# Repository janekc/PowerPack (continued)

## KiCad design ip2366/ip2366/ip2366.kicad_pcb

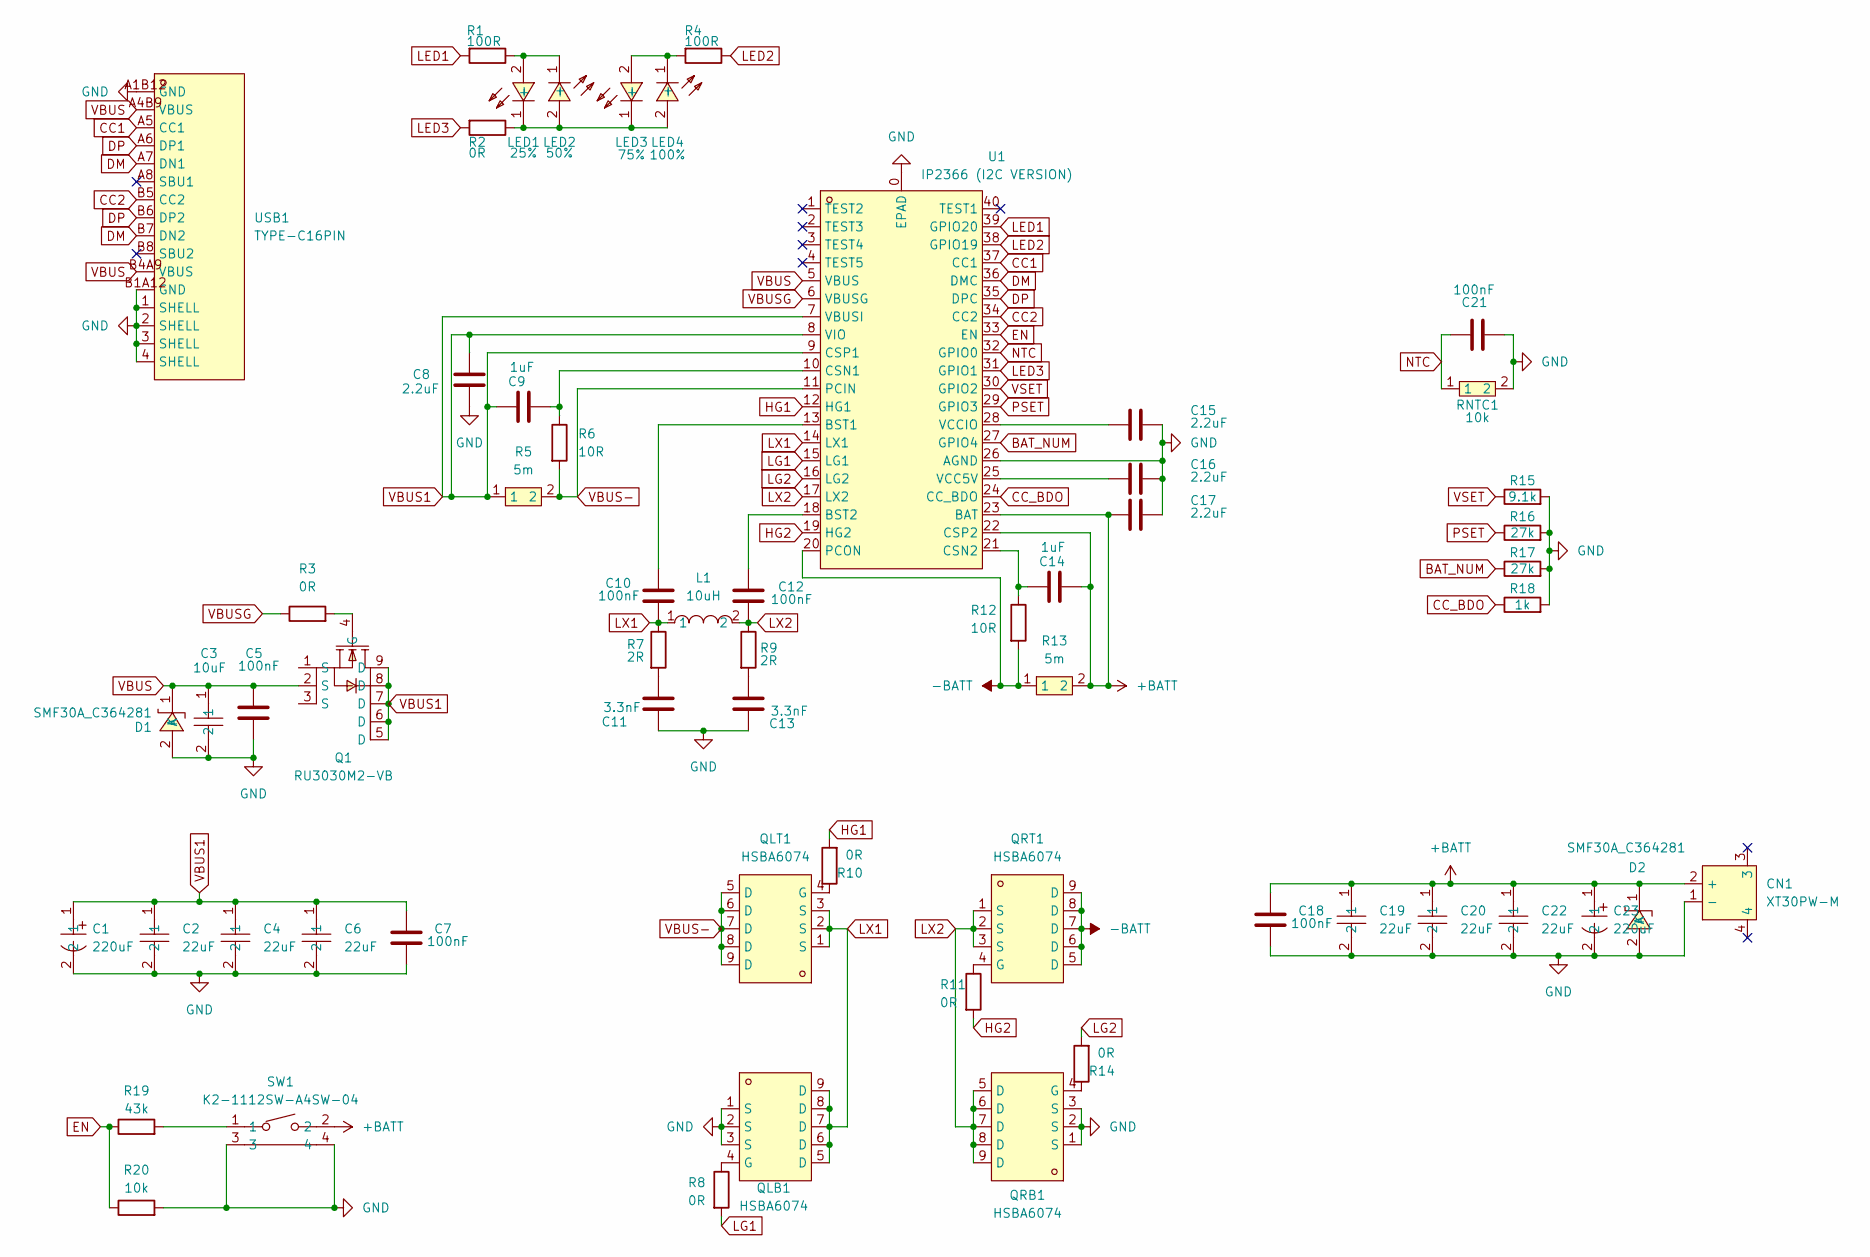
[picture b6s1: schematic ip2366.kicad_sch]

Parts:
C1, C23: 220uF; CAP-TH_BD8.0-P3.50-D0.6-FD; LCSC Part C2688260
C2, C4, C6, C19, C20, C22: 22uF; C1210; LCSC Part C778721
C3: 10uF; C1206; LCSC Part C89632
C5, C7, C10, C12, C18, C21: 100nF; C_0603_1608Metric_Pad1.08x0.95mm_HandSolder
C8, C15, C16, C17: 2.2uF; C_0603_1608Metric_Pad1.08x0.95mm_HandSolder
C9, C14: 1uF; C_0603_1608Metric_Pad1.08x0.95mm_HandSolder
C11, C13: 3.3nF; C_0603_1608Metric_Pad1.08x0.95mm_HandSolder
CN1: XT30PW-M; CONN-TH_XT30PW-M; LCSC Part C431092
D1, D2: SMF30A_C364281; SOD-123_L2.6-W1.6-LS3.5-RD; LCSC Part C364281
L1: 10uH; IND-SMD_L13.5-W12.5; LCSC Part C840531
LED1: 25%; LED0603-RD; LCSC Part C84265
LED2: 50%; LED0603-RD; LCSC Part C84265
LED3: 75%; LED0603-RD; LCSC Part C84265
LED4: 100%; LED0603-RD; LCSC Part C84265
Q1: RU3030M2-VB; DFN-8_L3.0-W3.0-P0.65-BL_VBQFXXXX; LCSC Part C19190164
QLB1: HSBA6074; DFN-8_L5.7-W5.1-P1.27-LS6.1-BL-2; LCSC Part C2903566
QLT1: HSBA6074; DFN-8_L5.7-W5.1-P1.27-LS6.1-BL-2; LCSC Part C2903566
QRB1: HSBA6074; DFN-8_L5.7-W5.1-P1.27-LS6.1-BL-2; LCSC Part C2903566
QRT1: HSBA6074; DFN-8_L5.7-W5.1-P1.27-LS6.1-BL-2; LCSC Part C2903566
R1, R4: 100R; R_0603_1608Metric_Pad0.98x0.95mm_HandSolder
R2, R3, R8, R10, R11, R14: 0R; R_0603_1608Metric_Pad0.98x0.95mm_HandSolder
R5, R13: 5m; R_2512_6332Metric_Pad1.40x3.35mm_HandSolder; LCSC Part C5123656
R6: 10R; R_0603_1608Metric_Pad0.98x0.95mm_HandSolder
R7, R9: 2R; R_0603_1608Metric_Pad0.98x0.95mm_HandSolder
R12: 10R; C_0603_1608Metric_Pad1.08x0.95mm_HandSolder
R15: 9.1k; R_0603_1608Metric_Pad0.98x0.95mm_HandSolder
R16, R17: 27k; R_0603_1608Metric_Pad0.98x0.95mm_HandSolder
R18: 1k; R_0603_1608Metric_Pad0.98x0.95mm_HandSolder
R19: 43k; R_0603_1608Metric_Pad0.98x0.95mm_HandSolder
R20: 10k; R_0603_1608Metric_Pad0.98x0.95mm_HandSolder
RNTC1: 10k; R0603; LCSC Part C98220
SW1: K2-1112SW-A4SW-04; KEY-TH_K2-1112SW-AXXW-XX; LCSC Part C223811
U1: IP2366 (I2C VERSION); QFN-40_L5.0-W5.0-P0.40-TL-EP3.7; LCSC Part C20415848
USB1: TYPE-C16PIN; USB-C-SMD_TYPE-C16PIN; LCSC Part C393939

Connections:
+BATT: C14.1, C17.2, C18.1, C19.1, C20.1, C22.1, C23.1, CN1.2 (+), D2.1 (K), R13.2, SW1.2, U1.22 (CSP2), U1.23 (BAT)
-BATT: QRT1.5 (D), QRT1.6 (D), QRT1.7 (D), QRT1.8 (D), QRT1.9 (D), R12.2, R13.1, U1.20 (PCON)
BAT_NUM: R17.1, U1.27 (GPIO4)
CC1: U1.37 (CC1), USB1.A5 (CC1)
CC2: U1.34 (CC2), USB1.B5 (CC2)
CC_BDO: R18.1, U1.24 (CC_BDO)
DM: U1.36 (DMC), USB1.A7 (DN1), USB1.B7 (DN2)
DP: U1.35 (DPC), USB1.A6 (DP1), USB1.B6 (DP2)
EN: R19.1, R20.1, U1.33 (EN)
GND: C1.2, C2.2, C3.2, C4.2, C5.2, C6.2, C7.2, C8.2, C11.2, C13.2, C15.1, C16.1, C17.1, C18.2, C19.2, C20.2, C21.2, C22.2, C23.2, CN1.1 (-), D1.2 (A), D2.2 (A), QLB1.1 (S), QLB1.2 (S), QLB1.3 (S), QRB1.1 (S), QRB1.2 (S), QRB1.3 (S), R15.2, R16.2, R17.2, R18.2, R20.2, RNTC1.2, SW1.3, SW1.4, U1.0 (EPAD), U1.26 (AGND), USB1.1 (SHELL), USB1.2 (SHELL), USB1.3 (SHELL), USB1.4 (SHELL), USB1.A1B12 (GND), USB1.B1A12 (GND)
HG1: R10.2, U1.12 (HG1)
HG2: R11.2, U1.19 (HG2)
LED1: R1.2, U1.39 (GPIO20)
LED2: R4.1, U1.38 (GPIO19)
LED3: R2.2, U1.31 (GPIO1)
LG1: R8.2, U1.15 (LG1)
LG2: R14.2, U1.16 (LG2)
LX1: C10.2, L1.1, QLB1.5 (D), QLB1.6 (D), QLB1.7 (D), QLB1.8 (D), QLB1.9 (D), QLT1.1 (S), QLT1.2 (S), QLT1.3 (S), R7.1, U1.14 (LX1)
LX2: C12.2, L1.2, QRB1.5 (D), QRB1.6 (D), QRB1.7 (D), QRB1.8 (D), QRB1.9 (D), QRT1.1 (S), QRT1.2 (S), QRT1.3 (S), R9.1, U1.17 (LX2)
unnamed: C11.1, R7.2
unnamed: C13.1, R9.2
unnamed: LED1.2 (+), LED2.1 (-), R1.1
unnamed: LED1.1 (-), LED2.2 (+), LED3.1 (-), LED4.2 (+), R2.1
unnamed: LED3.2 (+), LED4.1 (-), R4.2
unnamed: Q1.4 (G), R3.2
unnamed: QLB1.4 (G), R8.1
unnamed: QLT1.4 (G), R10.1
unnamed: QRB1.4 (G), R14.1
unnamed: QRT1.4 (G), R11.1
unnamed: R19.2, SW1.1
unnamed: C10.1, U1.13 (BST1)
unnamed: C12.1, U1.18 (BST2)
unnamed: C9.1, R6.1, U1.10 (CSN1)
unnamed: C14.2, R12.1, U1.21 (CSN2)
unnamed: C16.2, U1.25 (VCC5V)
unnamed: C15.2, U1.28 (VCCIO)
PSET: R16.1, U1.29 (GPIO3)
VBUS: C3.1, C5.1, D1.1 (K), Q1.1 (S), Q1.2 (S), Q1.3 (S), U1.5 (VBUS), USB1.A4B9 (VBUS), USB1.B4A9 (VBUS)
VBUS1: C1.1, C2.1, C4.1, C6.1, C7.1, C8.1, C9.2, Q1.5 (D), Q1.6 (D), Q1.7 (D), Q1.8 (D), Q1.9 (D), R5.1, U1.7 (VBUSI), U1.8 (VIO), U1.9 (CSP1)
VBUS-: QLT1.5 (D), QLT1.6 (D), QLT1.7 (D), QLT1.8 (D), QLT1.9 (D), R5.2, R6.2, U1.11 (PCIN)
VBUSG: R3.1, U1.6 (VBUSG)
VSET: R15.1, U1.30 (GPIO2)

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
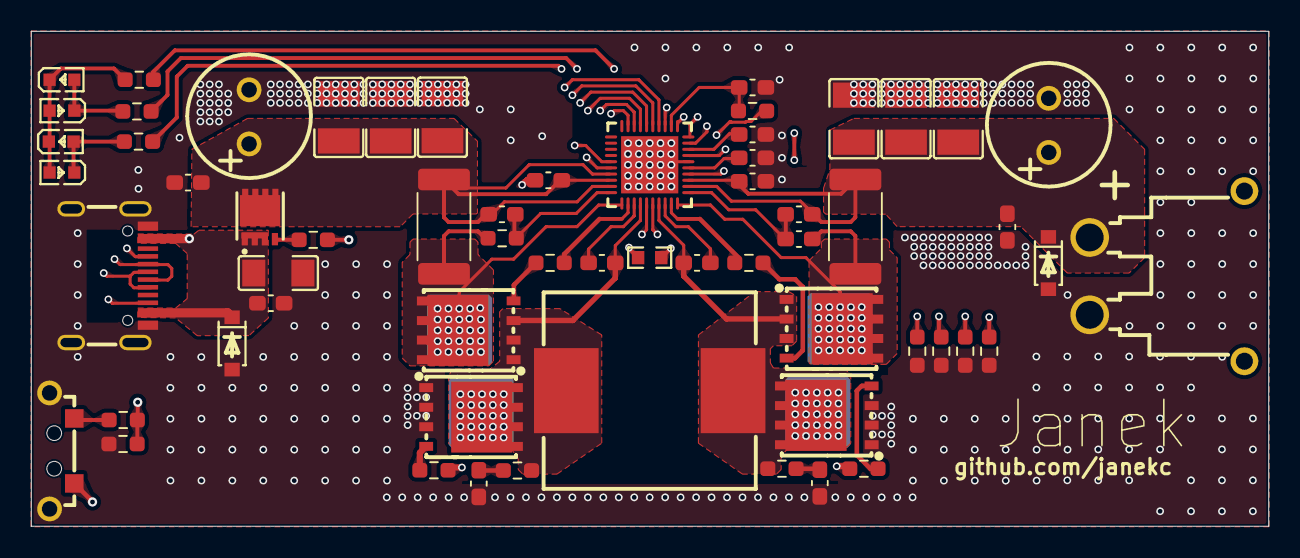
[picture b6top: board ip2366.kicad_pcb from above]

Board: 4 copper layers, 80.0 x 32.0 mm, 61 parts (0 on the bottom side), 44 nets.

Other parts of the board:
R21: 0R; R_0603_1608Metric_Pad0.98x0.95mm_HandSolder

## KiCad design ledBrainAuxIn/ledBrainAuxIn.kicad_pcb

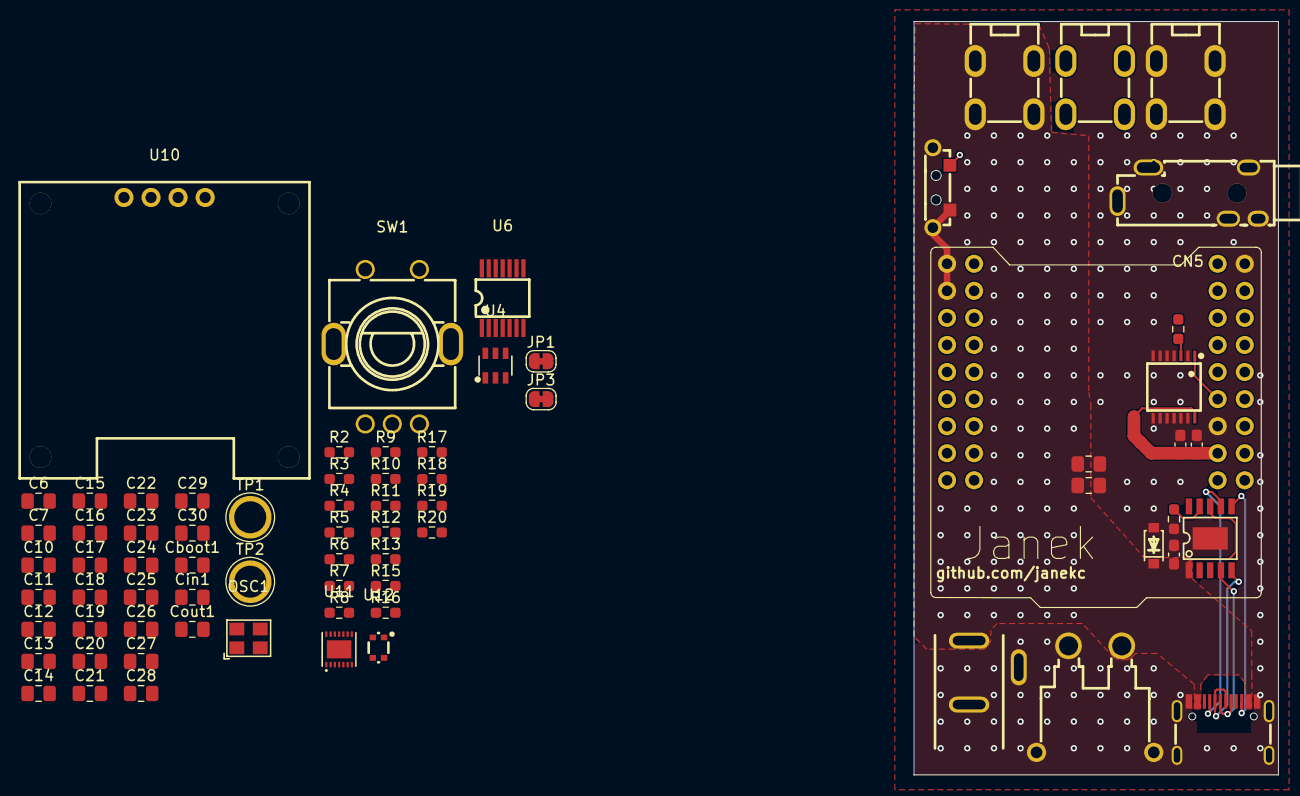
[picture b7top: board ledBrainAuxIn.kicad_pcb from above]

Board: 4 copper layers, 34.2 x 70.7 mm, 75 parts (1 on the bottom side), 49 nets.

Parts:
C1, C2: 0.1uF; C_0603_1608Metric_Pad1.08x0.95mm_HandSolder
C3: 1uF; C_0603_1608Metric_Pad1.08x0.95mm_HandSolder
C4, C5: 22uF; C_0805_2012Metric_Pad1.18x1.45mm_HandSolder
C6: 47pF; C_0805_2012Metric_Pad1.18x1.45mm_HandSolder
C7, C11, C15, C19: 100nF; C_0805_2012Metric_Pad1.18x1.45mm_HandSolder
C10, C12, C13, C14, C16, C17, C18: 10uF; C_0805_2012Metric_Pad1.18x1.45mm_HandSolder
C20: 15pF; C_0805_2012Metric_Pad1.18x1.45mm_HandSolder
C21, C22, C29, C30: 1uF; C_0805_2012Metric_Pad1.18x1.45mm_HandSolder
C23, C24, C25, C27, C28: 0.1uF; C_0805_2012Metric_Pad1.18x1.45mm_HandSolder
C26: 2.2uF; C_0805_2012Metric_Pad1.18x1.45mm_HandSolder
CN1: XT30PW-M; CONN-TH_XT30PW-M
CN5: PJ-328A0-B; AUDIO-TH_PJ-328A0-B
Cboot1: 1uF; C_0805_2012Metric_Pad1.18x1.45mm_HandSolder
Cin1: 10uF; C_0805_2012Metric_Pad1.18x1.45mm_HandSolder
Cout1: 10uF; C_0805_2012Metric_Pad1.18x1.45mm_HandSolder
D1: SMF30A_C364281; SOD-123_L2.6-W1.6-LS3.5-RD
DC1: DC-005-A200; DC-IN-TH_DC-005-A200
JP1, JP3: SolderJumper_2_Bridged; SolderJumper-2_P1.3mm_Bridged_RoundedPad1.0x1.5mm
OSC1: OT2EL4C4JI-111OLP-12.288M; OSC-SMD_4P-L3.2-W2.5-BL
R1: 62R; R_0603_1608Metric_Pad0.98x0.95mm_HandSolder
R2: 3.3M; R_0603_1608Metric_Pad0.98x0.95mm_HandSolder
R3: 5.1k; R_0603_1608Metric_Pad0.98x0.95mm_HandSolder
R4: 1k; R_0603_1608Metric_Pad0.98x0.95mm_HandSolder
R5, R6, R13, R16: 100R; R_0603_1608Metric_Pad0.98x0.95mm_HandSolder
R7, R8, R9, R10, R11, R12, R14, R15, R17, R18: 10k; R_0603_1608Metric_Pad0.98x0.95mm_HandSolder
R19: 150k or NC; R_0603_1608Metric_Pad0.98x0.95mm_HandSolder
R20: 100k or 0R; R_0603_1608Metric_Pad0.98x0.95mm_HandSolder
Rset1: 24k; R_0603_1608Metric_Pad0.98x0.95mm_HandSolder
SW1: EC11E09244BS; SW-TH_EC11XXXXXXXX
SW2: K2-1112SW-A4SW-04; KEY-TH_K2-1112SW-AXXW-XX
TP1: VDD; TestPoint_Plated_Hole_D3.0mm
TP2: GND; TestPoint_Plated_Hole_D3.0mm
U1: QuinLED-ESP32
U3: CH224A; ESSOP-10_L4.9-W3.9-P1.0-LS6.0-TL-EP
U4: ME3116; SOT-23-6_L2.9-W1.6-P0.95-LS2.8-BL
U5: SN74AHCT32QPWRQ1; TSSOP-14_L5.0-W4.4-P0.65-LS6.5-BL
U6: PCM1808PWR; TSSOP-14_L5.0-W4.4-P0.65-LS6.4-BL
U7, U8, U9: T34069; XFCN_PKT-TH_4P-T34069
U10: HS96L03W2C03; OLED-TH_L27.8-W27.2-P2.54_C9900033791
U11: MAX9814ETD+T; TDFN-14_L3.0-W3.0-P0.40-BL-EP
U12: NA-FFA381-A10-1; MIC-SMD_4P-L2.8-W1.9_NA-FFA381-A10-1
USB1: TYPE-C16PIN; USB-C-SMD_TYPE-C16PIN

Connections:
+3.3V: C17.1, C18.1, C19.1, C30.1, JP1.1 (A), OSC1.1 (Tri-state), OSC1.4 (VDD), R7.1, R8.1, R9.1, R15.1, R17.1, R18.1, U1.17 (3v3), U10.2 (VCC), U11.2 (~SHDN), U11.5 (VDD), U11.10 (GAIN)
+5V: C1.1, C2.2, C6.1, Cout1.2, JP3.1 (A), R3.1, R14.2, U1.26 (5v0), U5.14 (VCC)
AUDIO MCLK: C20.2, OSC1.3 (OUT), R5.2
AUDIO SCK: R16.1, U1.7 (IO14)
AUDIO SD: R13.1, U1.18 (IO13)
AUDIO WS: R6.2, U1.4 (IO35)
AUXIN_L: C16.1, CN5.2
AUXIN_R: C10.1, CN5.3
CC1: U3.7 (CC1), USB1.A5 (CC1)
CC2: U3.6 (CC2), USB1.B5 (CC2)
DISPLAY SCL: U1.31 (IO32), U10.3 (SCL)
DISPLAY SDA: U1.33 (IO_4), U10.4 (SDA)
DM: U3.5 (DM), USB1.A7 (DN1), USB1.B7 (DN2)
DP: U3.4 (DP), USB1.A6 (DP1), USB1.B6 (DP2)
GND: C1.2, C2.1, C3.2, C4.2, C5.2, C7.2, C11.2, C12.2, C13.2, C14.1, C15.1, C17.2, C18.2, C19.2, C20.1, C21.2, C23.1, C25.2, C26.2, C27.2, C28.2, C29.2, C30.2, CN1.1 (-), CN1.3, CN1.4, CN5.1, Cin1.2, Cout1.1, D1.2 (A), DC1.2, DC1.3, OSC1.2 (GND), R4.2, R10.2, R11.2, R12.2, R20.2, Rset1.1, SW1.6, SW1.7, SW1.C, SW1.D, SW2.2, SW2.3, SW2.4, TP2.1 (1_1), U1.1 (GND), U1.2 (GND*), U1.25 (GND), U1.28 (GND), U3.11 (GND), U4.2 (GND), U5.2 (1B), U5.4 (2A), U5.5 (2B), U5.6 (2Y), U5.7 (GND), U5.8 (3Y), U5.9 (3A), U5.10 (3B), U5.11 (4Y), U5.12 (4A), U5.13 (4B), U6.2 (AGND), U6.5 (DGND), U7.1, U7.2, U7.3, U7.4, U10.1 (GND), U11.7 (GND), U11.9 (A/R), U11.15 (EP), U12.2 (GND), U12.3 (GND), USB1.1 (SHELL), USB1.2 (SHELL), USB1.3 (SHELL), USB1.4 (SHELL), USB1.A1B12 (GND), USB1.B1A12 (GND)
LED1: U1.24 (IO16), U5.1 (1A)
LED DATA OUT: R1.1, U8.1, U8.2, U8.3, U8.4
MAINBUTTON: R14.1, SW2.1, U1.27 (IO15)
MIC AMP OUT: C22.2, CN5.10, CN5.11
MIC OUT: C24.2, U11.8 (MICIN)
MICBIAS: C23.2, R19.1, U11.13 (MICBIAS), U12.1 (VDD)
unnamed: Cboot1.2, U4.6 (SW)
unnamed: C14.2, C15.2, JP1.2 (B), U6.4 (VDD)
unnamed: C11.1, C13.1, JP3.2 (B), U6.3 (VCC)
unnamed: Rset1.2, U3.9 (CFG1)
unnamed: Cboot1.1, U4.1 (BS)
unnamed: R2.2, U4.4 (EN)
unnamed: C6.2, R3.2, R4.1, U4.3 (FB)
unnamed: R1.2, U5.3 (1Y)
unnamed: R16.2, U6.8 (BCK)
unnamed: R13.2, U6.9 (DOUT)
unnamed: R7.2, R10.1, U6.12 (FMT)
unnamed: R6.1, U6.7 (LRCK)
unnamed: R9.2, R12.1, U6.10 (MD0)
unnamed: R8.2, R11.1, U6.11 (MD1)
unnamed: R5.1, U6.6 (SCKI)
unnamed: C16.2, U6.13 (VINL)
unnamed: C10.2, U6.14 (VINR)
unnamed: C7.1, C12.1, U6.1 (VREF)
unnamed: C29.1, U11.12 (BIAS)
unnamed: C26.1, U11.3 (CG)
unnamed: C21.1, U11.1 (CT)
unnamed: C22.1, U11.6 (MICOUT)
unnamed: R19.2, R20.1, U11.14 (TH)
unnamed: C24.1, U12.4 (Output)
ROTARY BUTTON: C25.1, R18.2, SW1.E, U1.3 (S_VN)
ROTARY CLK: C28.1, R15.2, SW1.A, U1.6 (IO34)
ROTARY DT: C27.1, R17.2, SW1.B, U1.5 (IO33)
VBUS: C3.1, C4.1, C5.1, CN1.2 (+), Cin1.1, D1.1 (K), DC1.1, R2.1, TP1.1 (1_1), U3.1 (VHV), U3.8 (VBUS), U4.5 (IN), U9.1, U9.2, U9.3, U9.4, USB1.A4B9 (VBUS), USB1.B4A9 (VBUS)
